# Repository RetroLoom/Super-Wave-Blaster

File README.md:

# Super Wave Blaster

A hardware modification for converting 16-bit right-justified (EIAJ/SONY format) digital audio to I2S for use with high-quality PCM5102 DAC modules. Originally designed for the Super Nintendo/Super Famicom, this general-purpose converter also works with other devices like the Nintendo 64.

**MDFourier Measurements comparing to TOSLINK capture**

**Toslink -> Super Wave Blaster**

**Stock -> Super Wave Blaster**

More MDF measurements can be found in the Images directory. 

## Overview

The Super Nintendo uses the UPD6376 audio DAC with a 16-bit **right-justified** digital audio format (also known as EIAJ CD-350, SONY format, or Japanese format). This format uses three serial data lines, similar to the modern I2S standard. The Super Wave Blaster converts right-justified audio to I2S using a series of inverters and bit shifters to realign the digital data stream.

**What Gets Upgraded:**
- **DAC Module:** Upgrades the main audio output from the console's DSP (SPC700 on SNES)
- **Opamp Replacement:** Upgrades the mixed audio signal, which includes both the DSP audio AND external audio sources (cartridge expansion audio like SA-1, Super FX, etc.)

Since this is a general-purpose format converter, it can work with **other devices that output 16-bit right-justified audio**, including the **Nintendo 64**, which outputs the same format at various sample rates.

**Original design inspiration:** [EIAJ to I2S Converter Thread](https://www.diyaudio.com/community/threads/eiaj-to-i2s-converter-and-vice-versa.58564/)

## Features

- Direct digital audio conversion (16-bit right-justified → I2S)
- Compatible with popular PCM5102 DAC modules
- Works with SNES/Super Famicom and other 16-bit right-justified sources (e.g., Nintendo 64)
- Cleaner, higher-fidelity audio output
- Configurable for different SNES revisions
- Optional analog signal chain upgrades

## Installation Overview

1. Install the Super Wave Blaster DAC module
2. (Recommended) Upgrade analog mixing components
3. Configure DAC output settings for your SNES revision
4. Test and enjoy improved audio quality

## Recommended Upgrades

While the DAC replacement provides digital conversion benefits, upgrading the entire analog audio signal chain can have an even greater impact on sound quality. Consider these upgrades for optimal results:

### 1. Mixing Opamp Replacement

**Recommended Models:**
- **OPA1652AIDR** (dual opamp)
- **OPA1654AIDR** (quad opamp)
- Or similar audiophile-grade opamps

**Compatibility by SNES Revision:**
- **SHVC revisions (modular):** Uses two dual LM2904 opamps
- **GPM revisions:** Uses one quad LM324 opamp
- **RGB revisions (S-Mix chip):** Not drop-in compatible - use the [Super ReMix replacement board](https://github.com/RetroLoom/Super-ReMix) for OPA16xx compatibility

**Benefits:** Reduced noise and distortion, particularly in high-frequency detail

### 2. Audio Transistor Upgrade

**Location:** Q16 and Q17 (not present on S-Mix versions)

**Original:** C2412 transistors  
**Recommended:** MMBT5088LT1G transistors

**Advanced Option:** When using OPA16xx series opamps, these transistors can be bypassed entirely for the most accurate sound. The OPA16xx has sufficient drive capability for standard line-level outputs.

**When to keep transistors:**
- Using lower impedance outputs (headphones)
- Driving passive speakers
- Prefer the "colored" sound signature the transistors provide

**Note:** The original transistors were likely included to boost current drive when paired with the weaker LM324 opamp.

### 3. Output Coupling Capacitors

**Original:** 10µF electrolytic capacitors  
**Recommended:** Low-ESR polymer capacitors

**Specific Recommendation:**  
Wurth Elektronik 875105240001
- Capacitance: 10µF
- ESR: 45mΩ
- Diameter: 4mm

⚠️ **Important:** Verify capacitor dimensions for your specific SNES revision before ordering.

## DAC Output Configuration

The DAC module configuration depends on your SNES revision and mixing opamp choice. Select the appropriate configuration below:

### Configuration A: LM324 or OPA16xx Opamps

**Jumper Settings:**
- JP1: **Open**
- JP2: **Open**

**Resistors:**
- R3, R4: **Do not populate**
- R5, R6: **24kΩ** (for unity gain from PCM5102A)

**Gain Control:** Adjusted via R5/R6 and opamp feedback resistors

---

### Configuration B: S-Mix Chip

**Jumper Settings:**
- JP1: **Closed**
- JP2: **Closed**

**Resistors:**
- R3, R4: **10kΩ**
- R5, R6: **Do not populate**

**Capacitors:**
- C15, C16: **470pF** (replaces default values)

**Important:** The S-Mix has its own gain network. The voltage divider created by R3/R4 prevents clipping and overdriving the signal.

## Bill of Materials

### Core DAC Module Components (Both Configurations)

| Designator | Component | Value/Part | Package | Qty | Notes |
|------------|-----------|------------|---------|-----|-------|
| U5 | DAC | PCM5102A | TSSOP-20 | 1 | Main I2S DAC chip |
| U2 | Inverter | CD74HCT14PWR | TSSOP-14 | 1 | Schmitt trigger hex inverter |
| U3 | Shift Register | SN74HC595PWR | TSSOP-16 | 1 | 8-bit shift register |
| U4 | Level Shifter | SN74LVC8T245PWR | TSSOP-24 | 1 | 8-bit dual-supply translator |
| U1 | Voltage Regulator | TLV73333PDBV | SOT-23-5 | 1 | 3.3V LDO regulator |
| C1, C2 | Capacitor | 10µF | 0805 | 2 | Power supply filtering |
| C3-C11 | Capacitor | 0.1µF | 0805 | 8 | Decoupling capacitors |
| C12, C10 | Capacitor | 2.2µF | 0805 | 2 | Additional filtering |
| R1-R2 | Resistor | 470Ω | 0805 | 2 | Series/termination resistors |
| JP1, JP2 | Solder Jumper | - | 2mm pitch | 2 | Configuration selection |

### Configuration-Specific Components

#### Configuration A: LM324 / OPA16xx Opamps

**Jumper Settings:** JP1 **Open**, JP2 **Open**

| Designator | Component | Value | Package | Qty | Notes |
|------------|-----------|-------|---------|-----|-------|
| R3, R4 | Resistor | - | 0805 | 0 | **Do not populate** |
| R5, R6 | Resistor | **24kΩ** | 0805 | 2 | Unity gain from PCM5102A |
| C15, C16 | Capacitor | 2.2nF | 0805 | 2 | low pass filter cap |
| C13, C14 | Capacitor | **1µF, X7R** | 0805 | 2 | Opamp input coupling |

#### Configuration B: S-Mix Chip

**Jumper Settings:** JP1 **Closed**, JP2 **Closed**

| Designator | Component | Value | Package | Qty | Notes |
|------------|-----------|-------|---------|-----|-------|
| R1, R2 | Resistor | **20kΩ** | 0805 | 2 | **Only for S-Mix (Config B)** -voltage divider |
| R3, R4 | Resistor | 10kΩ | 0805 | 2 | **Only for S-Mix (Config B)** - voltage divider |
| R5, R6 | Resistor | **0Ω** (optional) | 0805 | 2 | Jumper 1 and 2 to bypass |
| C15, C16 | Capacitor | **470pF** | 0805 | 2 | **Replace default 2.2nF** |
| C13, C14 | Capacitor | **0.1µF, X7R** | 0805 | 2 | S-Mix input coupling |

**All Resistors:**
- Size: 0805 (2012 metric)
- Power: 1/8W minimum
- Tolerance: 1% recommended for better channel matching

**Full BOM Available:**
Mouser Project: [View Complete BOM](https://www.mouser.com/Tools/Project/Details?projectGUID=576ace13-fcfc-4374-9011-b2b0ae4ebff9)

⚠️ **Important:** The Mouser project includes components for multiple SNES revisions and both configurations. Select components based on your specific console revision and chosen configuration (A or B).

## Revision Compatibility

| SNES Revision | Opamp Type | Configuration | Notes |
|---------------|------------|---------------|-------|
| SHVC (Modular) | 2× LM2904 (dual) | A | Standard upgrade path |
| GPM | 1× LM324 (quad) | A | Standard upgrade path |
| RGB (S-Mix) | S-Mix chip | B | Requires voltage divider, or use [Super ReMix replacement](https://github.com/RetroLoom/Super-ReMix) |

## Other Compatible Devices

Since the Super Wave Blaster is a general-purpose **16-bit right-justified to I2S converter**, it can work with other gaming consoles and devices that output audio in the same format:

**Nintendo 64:**
- Outputs 16-bit right-justified audio at various sample rates (22.05 kHz to 48 kHz depending on the game)
- Successfully tested with SNES digital audio mods
- Requires tapping the digital audio signals from the N64's audio DAC
- Consider adding series termination resistors at the RCP's digital audio output for improved signal integrity

**Note:** Installation methods and connection points will vary by device. Consult device-specific documentation for proper digital audio tap points.

## Troubleshooting

**No audio output:**
- Verify jumper settings match your revision
- Check DAC module power connections
- Confirm proper solder joints

**Audio too loud/clipping:**
- S-Mix users: Ensure R3/R4 are populated and JP1/JP2 are closed
- Check C15/C16 values (470pF for S-Mix)

**Audio too quiet:**
- LM324/OPA users: Verify JP1/JP2 are open
- Check R5/R6 values (24kΩ for unity gain)

## Contributing

Contributions, suggestions, and improvements are welcome! Please open an issue or pull request.

## Disclaimer and Warranty

**This project is provided "as-is" without any warranty of any kind, either expressed or implied.**

By using this modification, you acknowledge and agree that:

- This is an **experimental hardware modification** that requires soldering and electronics knowledge
- Installation may **void your console's warranty** (if still applicable)
- Improper installation can **damage your console** permanently
- The author(s) are **not responsible** for any damage to your equipment, including but not limited to:
  - Damage to the gaming console
  - Damage to connected audio equipment
  - Loss of game saves or data
  - Personal injury from soldering equipment
- **You perform this modification at your own risk**
- Different console revisions may have different requirements - verify compatibility before proceeding
- While this design has been tested, **results may vary** based on your specific hardware revision, component quality, and installation skill
- The author(s) provide **no guarantee** that this modification will work with your specific console or meet your expectations

**Recommendation:** If you are uncomfortable with electronics modification or soldering surface-mount components, consider seeking assistance from a professional modding service.

## License

The hardware portions of this repository are licensed under the **CERN OHL version 2 - Strongly Reciprocal**.

[Full License Text](https://ohwr.org/project/cernohl/-/wikis/uploads/819d71bea3458f71fba6cf4fb0f2de6b/cern_ohl_s_v2.txt)

**Note:** This license allows you to use, modify, and distribute this hardware design, but any modifications or derivative works must also be released under the same license.

## Acknowledgments

- Original EIAJ to I2S conversion circuit design from the [diyaudio.com community](https://www.diyaudio.com/community/threads/eiaj-to-i2s-converter-and-vice-versa.58564/)
- Super Nintendo/Famicom hardware community

---

**Questions or issues?** Please open a GitHub issue for support.

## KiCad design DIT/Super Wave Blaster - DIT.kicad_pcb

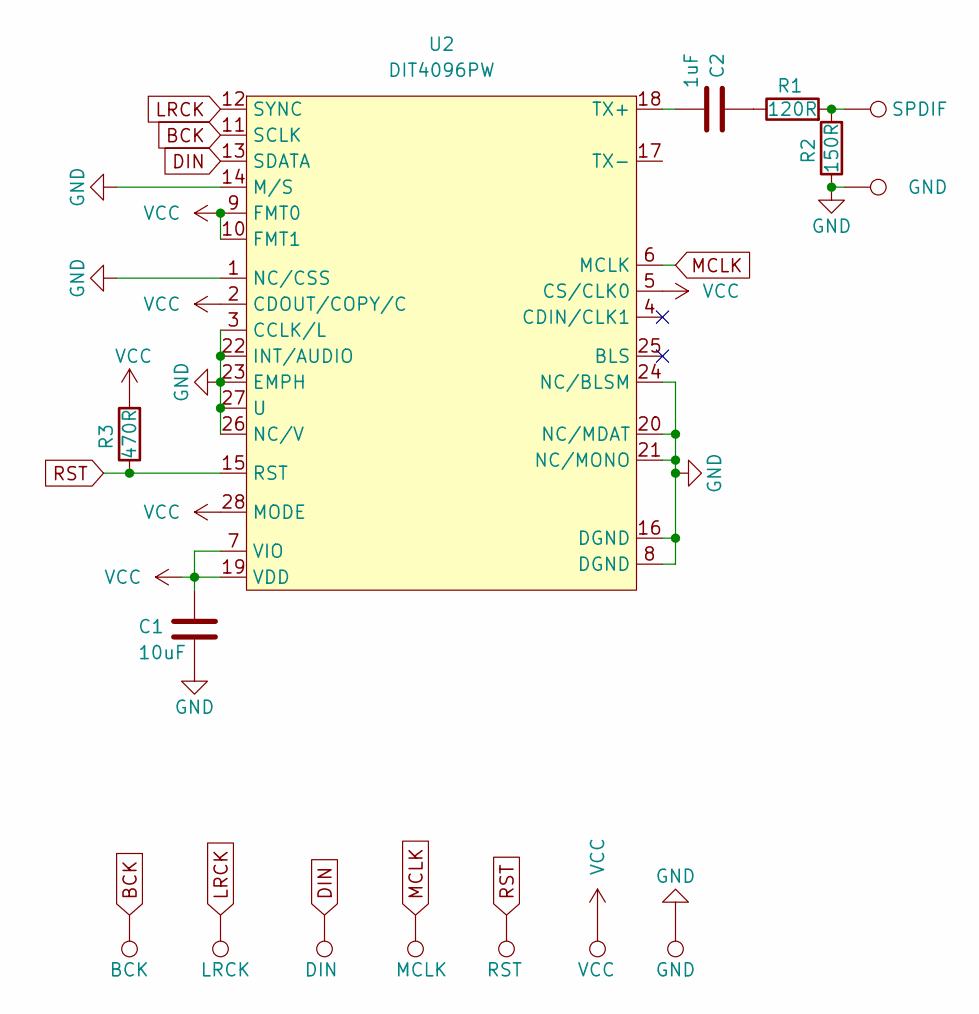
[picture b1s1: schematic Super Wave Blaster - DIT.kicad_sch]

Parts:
C1: 10uF; C_0805_2012Metric_Pad1.18x1.45mm_HandSolder
C2: 1uF; C_0805_2012Metric_Pad1.18x1.45mm_HandSolder
R1: 120R; R_0805_2012Metric_Pad1.20x1.40mm_HandSolder
R2: 150R; R_0805_2012Metric_Pad1.20x1.40mm_HandSolder
R3: 470R; R_0805_2012Metric_Pad1.20x1.40mm_HandSolder
TP1: BCK; TestPoint_Pad_1.0x1.0mm
TP2: LRCK; TestPoint_Pad_1.0x1.0mm
TP3: DIN; TestPoint_Pad_1.0x1.0mm
TP4: MCLK; TestPoint_Pad_1.0x1.0mm
TP5: RST; TestPoint_Pad_1.0x1.0mm
TP6: SPDIF; TestPoint_Pad_1.0x1.0mm
TP7, TP9: GND; TestPoint_Pad_1.0x1.0mm
TP8: VCC; TestPoint_Pad_1.0x1.0mm
U2: DIT4096PW; SSOP-28_5.3x10.2mm_P0.65mm

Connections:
BCK: TP1.1, U2.11 (SCLK)
DIN: TP3.1, U2.13 (SDATA)
GND: C1.2, R2.1, TP7.1, TP9.1, U2.1 (NC/CSS), U2.3 (CCLK/L), U2.8 (DGND), U2.14 (M/S), U2.16 (DGND), U2.20 (NC/MDAT), U2.21 (NC/MONO), U2.22 (INT/AUDIO), U2.23 (EMPH), U2.24 (NC/BLSM), U2.26 (NC/V), U2.27 (U)
LRCK: TP2.1, U2.12 (SYNC)
MCLK: TP4.1, U2.6 (MCLK)
unnamed: C2.1, R1.1
unnamed: R1.2, R2.2, TP6.1
unnamed: C2.2, U2.18 (TX+)
RST: R3.1, TP5.1, U2.15 (RST)
VCC: C1.1, R3.2, TP8.1, U2.2 (CDOUT/COPY/C), U2.5 (CS/CLK0), U2.7 (VIO), U2.9 (FMT0), U2.10 (FMT1), U2.19 (VDD), U2.28 (MODE)

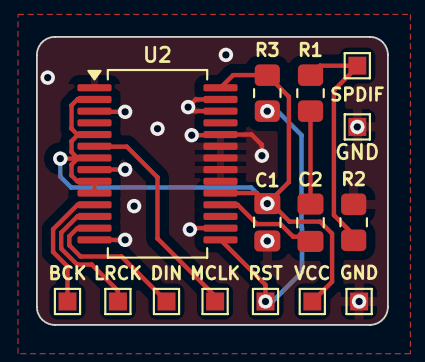
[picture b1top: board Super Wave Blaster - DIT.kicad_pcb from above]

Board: 2 copper layers, 19.5 x 16.0 mm, 15 parts (0 on the bottom side), 10 nets.

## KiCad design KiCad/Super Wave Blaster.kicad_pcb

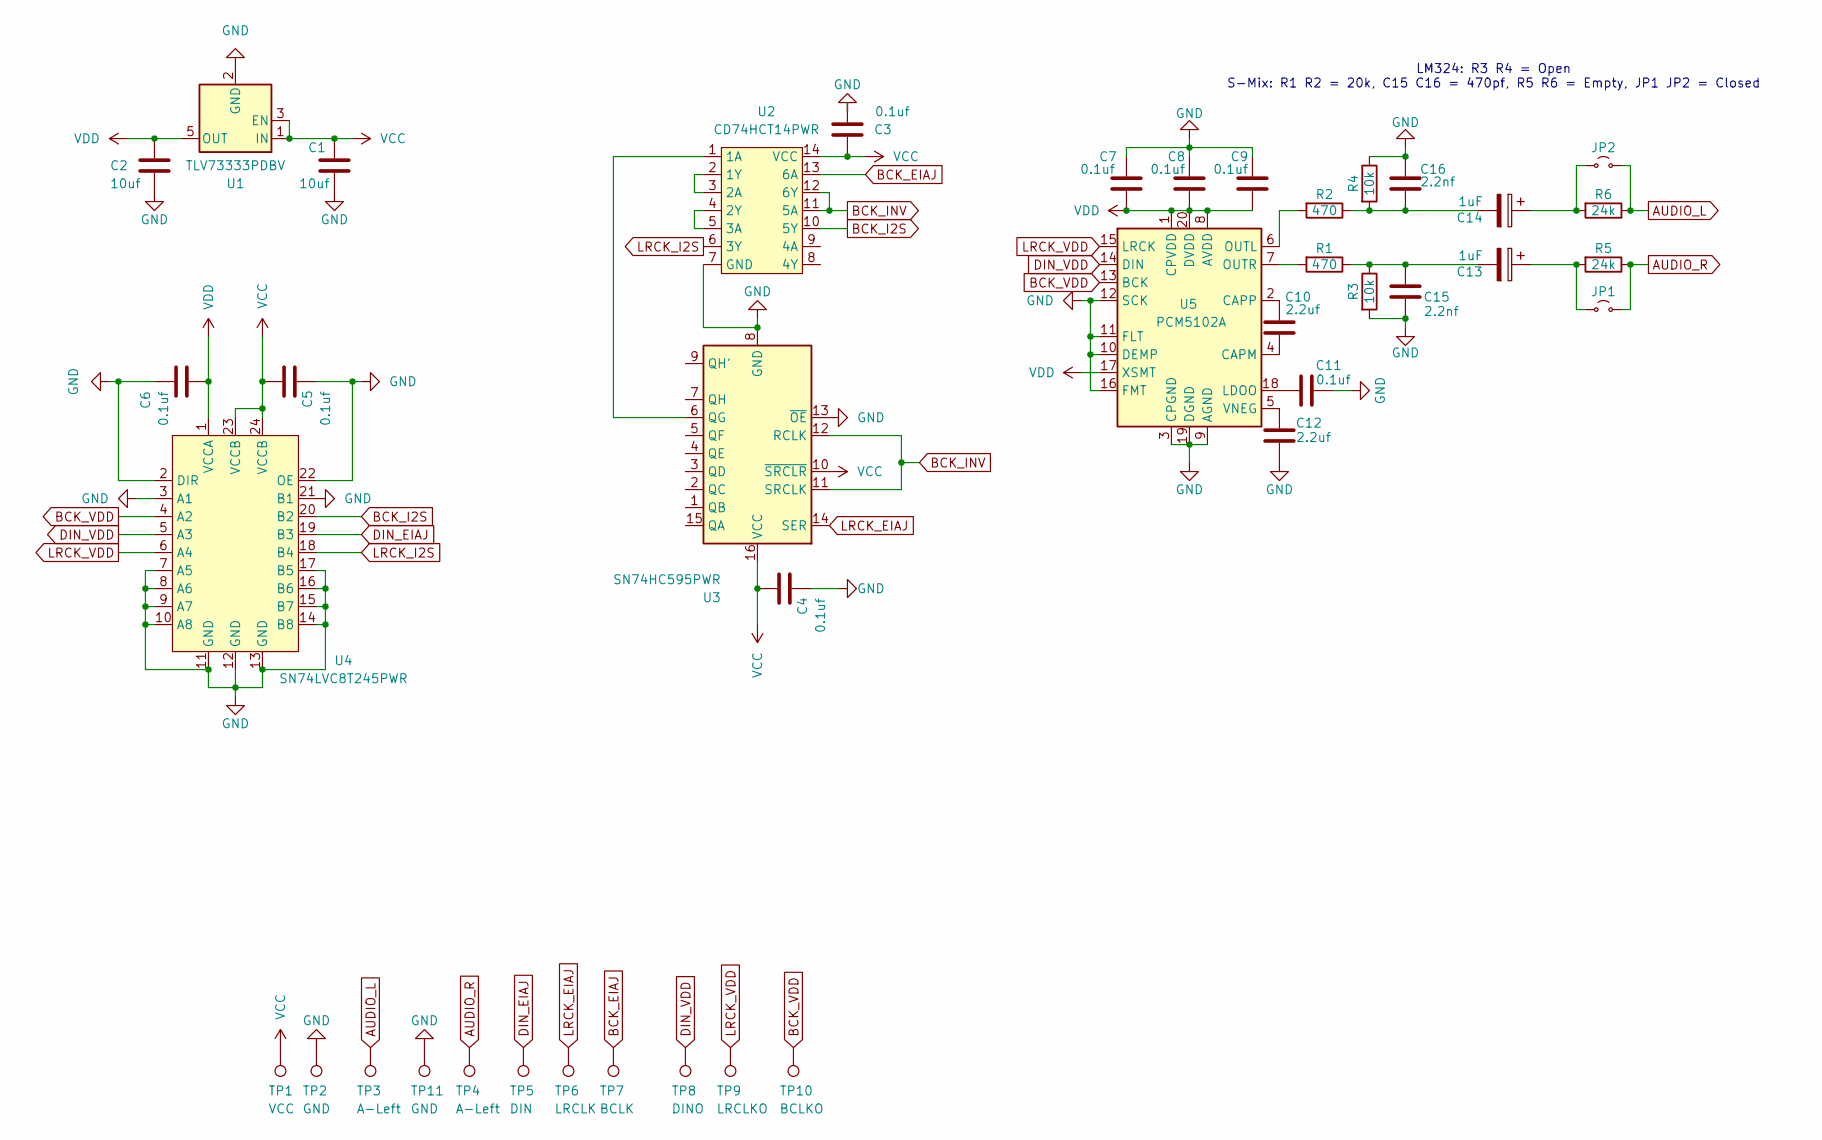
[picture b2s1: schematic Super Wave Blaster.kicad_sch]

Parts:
C1, C2: 10uf; C_0805_2012Metric_Pad1.18x1.45mm_HandSolder
C3, C4, C5, C6, C7, C8, C9, C11: 0.1uf; C_0805_2012Metric_Pad1.18x1.45mm_HandSolder
C10, C12: 2.2uf; C_0805_2012Metric_Pad1.18x1.45mm_HandSolder
C13, C14: 1uF; C_0805_2012Metric_Pad1.18x1.45mm_HandSolder
C15, C16: 2.2nf; C_0805_2012Metric_Pad1.18x1.45mm_HandSolder
JP1, JP2: SolderJumper-2_P1.3mm_Open_RoundedPad1.0x1.5mm
R1, R2: 470; R_0805_2012Metric_Pad1.20x1.40mm_HandSolder
R3, R4: 10k; R_0805_2012Metric_Pad1.20x1.40mm_HandSolder
R5, R6: 24k; R_0805_2012Metric_Pad1.20x1.40mm_HandSolder
TP1: VCC; TestPoint_Pad_1.5x1.5mm
TP2, TP11: GND; TestPoint_Pad_1.5x1.5mm
TP3, TP4: A-Left; TestPoint_Pad_1.5x1.5mm
TP5: DIN; TestPoint_Pad_1.5x1.5mm
TP6: LRCLK; TestPoint_Pad_1.5x1.5mm
TP7: BCLK; TestPoint_Pad_1.5x1.5mm
TP8: DINO; TestPoint_Pad_1.5x1.5mm
TP9: LRCLKO; TestPoint_Pad_1.5x1.5mm
TP10: BCLKO; TestPoint_Pad_1.5x1.5mm
U1: TLV73333PDBV; SOT-23-5
U2: CD74HCT14PWR; TSSOP-14_4.4x5mm_P0.65mm
U3: SN74HC595PWR; TSSOP-16_4.4x5mm_P0.65mm
U4: SN74LVC8T245PWR; TSSOP-24_4.4x7.8mm_P0.65mm
U5: PCM5102A; TSSOP-20_4.4x6.5mm_P0.65mm

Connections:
AUDIO_L: JP2.2 (B), R6.1, TP3.1
AUDIO_R: JP1.2 (B), R5.1, TP4.1
BCK_EIAJ: TP7.1, U2.13 (6A)
BCK_I2S: U2.10 (5Y), U4.20 (B2)
BCK_INV: U2.11 (5A), U2.12 (6Y), U3.11 (SRCLK), U3.12 (RCLK)
BCK_VDD: TP10.1, U4.4 (A2), U5.13 (BCK)
DIN_EIAJ: TP5.1, U4.19 (B3)
DIN_VDD: TP8.1, U4.5 (A3), U5.14 (DIN)
GND: C1.2, C2.2, C3.2, C4.2, C5.2, C6.2, C7.2, C8.2, C9.2, C11.2, C12.1, C15.1, C16.2, R3.2, R4.1, TP2.1, TP11.1, U1.2 (GND), U2.7 (GND), U3.8 (GND), U3.13 (~OE), U4.2 (DIR), U4.3 (A1), U4.7 (A5), U4.8 (A6), U4.9 (A7), U4.10 (A8), U4.11 (GND), U4.12 (GND), U4.13 (GND), U4.14 (B8), U4.15 (B7), U4.16 (B6), U4.17 (B5), U4.21 (B1), U4.22 (OE), U5.3 (CPGND), U5.9 (AGND), U5.10 (DEMP), U5.11 (FLT), U5.12 (SCK), U5.16 (FMT), U5.19 (DGND)
LRCK_EIAJ: TP6.1, U3.14 (SER)
LRCK_I2S: U2.6 (3Y), U4.18 (B4)
LRCK_VDD: TP9.1, U4.6 (A4), U5.15 (LRCK)
unnamed: C13.2, C15.2, R1.1, R3.1
unnamed: C14.2, C16.1, R2.1, R4.2
unnamed: C13.1, JP1.1 (A), R5.2
unnamed: C14.1, JP2.1 (A), R6.2
unnamed: U2.1 (1A), U3.6 (QG)
unnamed: U2.2 (1Y), U2.3 (2A)
unnamed: U2.4 (2Y), U2.5 (3A)
unnamed: C10.1, U5.4 (CAPM)
unnamed: C10.2, U5.2 (CAPP)
unnamed: C11.1, U5.18 (LDOO)
unnamed: R2.2, U5.6 (OUTL)
unnamed: R1.2, U5.7 (OUTR)
unnamed: C12.2, U5.5 (VNEG)
VCC: C1.1, C3.1, C4.1, C5.1, TP1.1, U1.1 (IN), U1.3 (EN), U2.14 (VCC), U3.10 (~SRCLR), U3.16 (VCC), U4.23 (VCCB), U4.24 (VCCB)
VDD: C2.1, C6.1, C7.1, C8.1, C9.1, U1.5 (OUT), U4.1 (VCCA), U5.1 (CPVDD), U5.8 (AVDD), U5.17 (XSMT), U5.20 (DVDD)

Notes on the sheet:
LM324: R3 R4 = Open S-Mix: R1 R2 = 20k, C15 C16 = 470pf, R5 R6 = Empty, JP1 JP2 = Closed

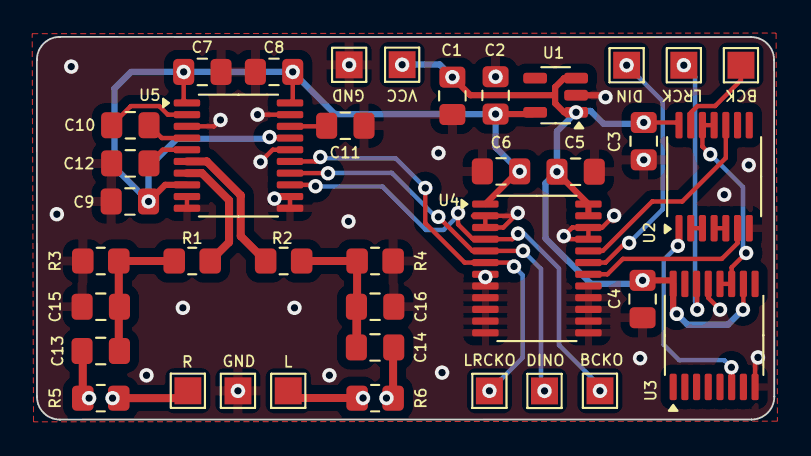
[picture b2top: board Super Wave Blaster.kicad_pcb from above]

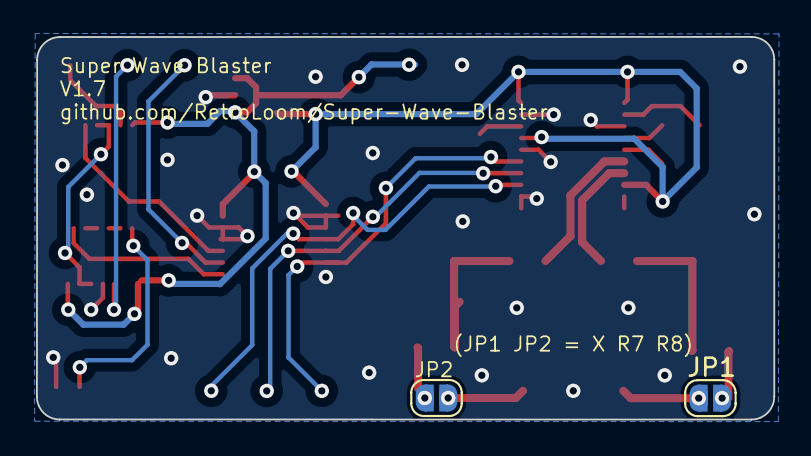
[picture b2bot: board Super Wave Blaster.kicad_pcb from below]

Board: 2 copper layers, 41.0 x 21.3 mm, 40 parts (2 on the bottom side), 27 nets.

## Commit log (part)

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2025-01-22 Initial Design - v1.0
2025-01-27 Add labels to audio headers
2025-01-27 Cleanup ground plane
2025-01-29 Upload general images and RGB revision installation
2025-01-29 Revision v1.1
2025-01-29 Remove Silkscreen blob
2025-01-29 Tighten up traces and ground
2025-01-29 Ignore gerber export folder
2025-01-30 Cleanup schematic layout
2025-01-30 Add and organize images
2025-01-30 Proof Readme
2025-01-30 Update License
2025-01-31 Update file metadata
2025-01-31 Moved opamp output for better positioning
2025-01-31 Tighten up new layout
2025-01-31 V1.2
2025-01-31 Update 3D Image
2025-01-31 Slight shift opamp out
2025-01-31 Label cleanup
2025-02-01 Update readme and images
2025-02-01 Another layout shift, opamp out moved for more convenient wiring
2025-02-01 V1.3
2025-02-01 Small shift to EIAJ pin header
2025-02-03 Update Readme - Mouser Project, 3D Image Fix
2025-02-03 Readme update - S-Mix notes
2025-02-04 Added gain control / high pass filter section to readme
2025-02-24 V1.4
    Adjust J7 opamp outputs, cleaned up ground plane, changed all 0805 pads to hand solder sizing.
2025-02-24 Update copper fill planes
2025-07-19 V1.5
    Refactored for underside mounting only and optional expansion for S/PDIF output. Full PCM5102A integration. Optimized audio quality.
2025-07-19 Change S-Mix values, jumper notes
2025-07-19 Clean up old images, add v1.6 images
2025-07-19 V1.6
    Refactor analog circuit with 0.1uf coupling and 100k pull down.
2025-07-19 Add BOM inclusion
2025-07-19 Update readme and documentation
2025-08-14 Official Public Release - v1.6
2026-02-05 Update README and schematic documentation. Save with newer version of Kicad
2026-02-05 Fix typos and BOM for configurations
2026-02-05 One more typo fix in README
2026-02-05 v1.7 - Fix issue with high pass pole, add MDF measurements, update layout for changes with X7R coupling caps
2026-02-05 Fix readme image layout
2026-02-06 Add MDF wav file, better comparison images for toslink and stock
2026-05-03 DIT: Move vias off component pads
2026-05-03 DIT v0.2 - compact and right justified only
2026-05-03 Initial DIT board
